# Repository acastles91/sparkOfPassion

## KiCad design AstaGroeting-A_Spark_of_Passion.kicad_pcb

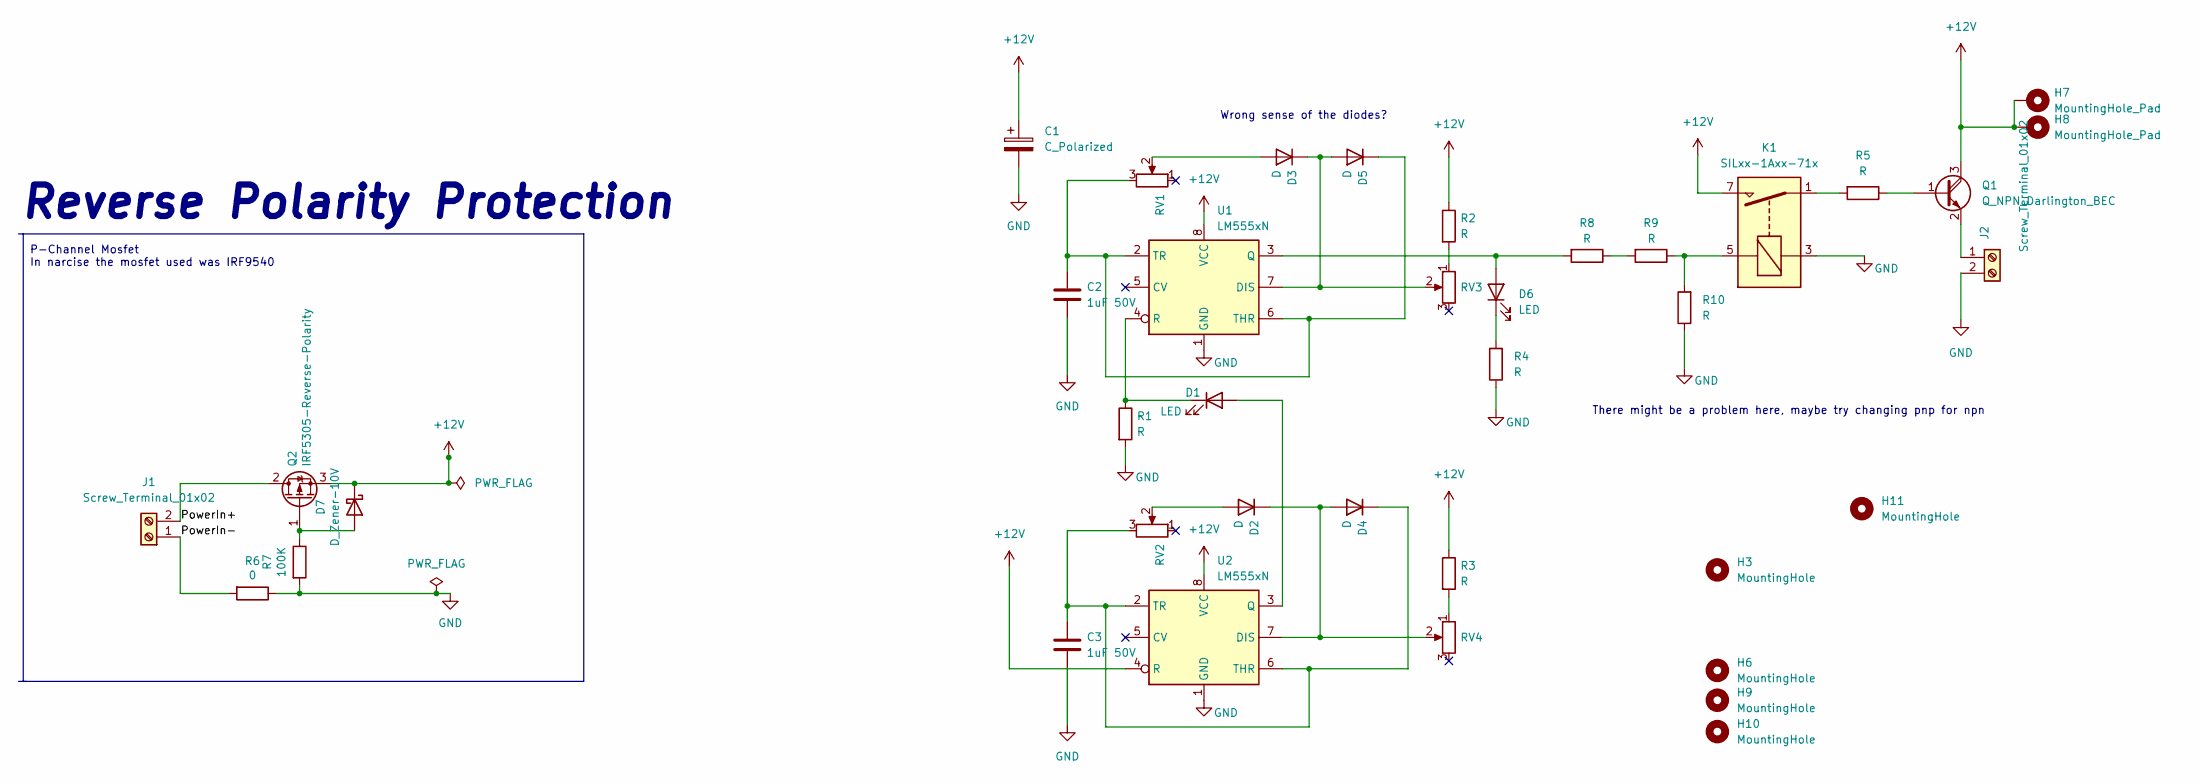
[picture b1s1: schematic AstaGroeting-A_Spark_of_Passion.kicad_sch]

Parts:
C1: C_Polarized; CP_Radial_D13.0mm_P5.00mm
C2, C3: 1uF 50V; CP_Radial_D4.0mm_P2.00mm
D1, D6: LED; LED_D3.0mm
D2, D3, D4, D5: D; D_A-405_P10.16mm_Horizontal
D7: D_Zener-10V; D_DO-35_SOD27_P7.62mm_Horizontal
H3, H6, H9, H10, H11: MountingHole; MountingHole_3.2mm_M3_Pad_Via
H7, H8: MountingHole_Pad; MountingHole_4.3mm_M4_Pad_Via
J1, J2: Screw_Terminal_01x02; TerminalBlock_Altech_AK300-2_P5.00mm
K1: SILxx-1Axx-71x; Relay_SPST_StandexMeder_SIL_Form1A
Q1: Q_NPN_Darlington_BEC; TO-3
Q2: IRF5305-Reverse-Polarity; TO-220-3_Horizontal_TabDown
R1, R2, R3, R4, R5, R8, R9, R10: R; R_Axial_DIN0207_L6.3mm_D2.5mm_P10.16mm_Horizontal
R6: 0; R_Axial_DIN0207_L6.3mm_D2.5mm_P10.16mm_Horizontal
R7: 100K; R_Axial_DIN0207_L6.3mm_D2.5mm_P10.16mm_Horizontal
RV1, RV2, RV3, RV4: R_Potentiometer; Potentiometer_Bourns_3296W_Vertical
U1, U2: LM555xN; DIP-8_W7.62mm

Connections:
+12V: C1.1, D7.1 (K), H7.1, H8.1, K1.7, Q1.3 (C), Q2.3 (S), R2.1, R3.1, U1.8 (VCC), U2.4 (R), U2.8 (VCC)
/PowerIn+: J1.2, Q2.2 (D)
/PowerIn-: J1.1, R6.2
GND: C1.2, C2.2, C3.2, J2.2, K1.3, R1.2, R4.1, R6.1, R7.2, R10.1, U1.1 (GND), U2.1 (GND)
unnamed: C2.1, D5.1 (K), RV1.3, U1.2 (TR), U1.6 (THR)
unnamed: C3.1, D4.1 (K), RV2.3, U2.2 (TR), U2.6 (THR)
unnamed: D1.1 (K), R1.1, U1.4 (R)
unnamed: D1.2 (A), U2.3 (Q)
unnamed: D2.1 (K), D4.2 (A), RV4.2, U2.7 (DIS)
unnamed: D2.2 (A), RV2.2
unnamed: D3.1 (K), D5.2 (A), RV3.2, U1.7 (DIS)
unnamed: D3.2 (A), RV1.2
unnamed: D6.1 (K), R4.2
unnamed: D6.2 (A), R8.2, U1.3 (Q)
unnamed: D7.2 (A), Q2.1 (G), R7.1
unnamed: K1.1, R5.2
unnamed: K1.5, R9.1, R10.2
unnamed: Q1.1 (B), R5.1
unnamed: J2.1, Q1.2 (E)
unnamed: R2.2, RV3.1
unnamed: R3.2, RV4.1
unnamed: R8.1, R9.2

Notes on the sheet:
Reverse Polarity Protection
Wrong sense of the diodes?
There might be a problem here, maybe try changing pnp for npn
P-Channel Mosfet In narcise the mosfet used was IRF9540

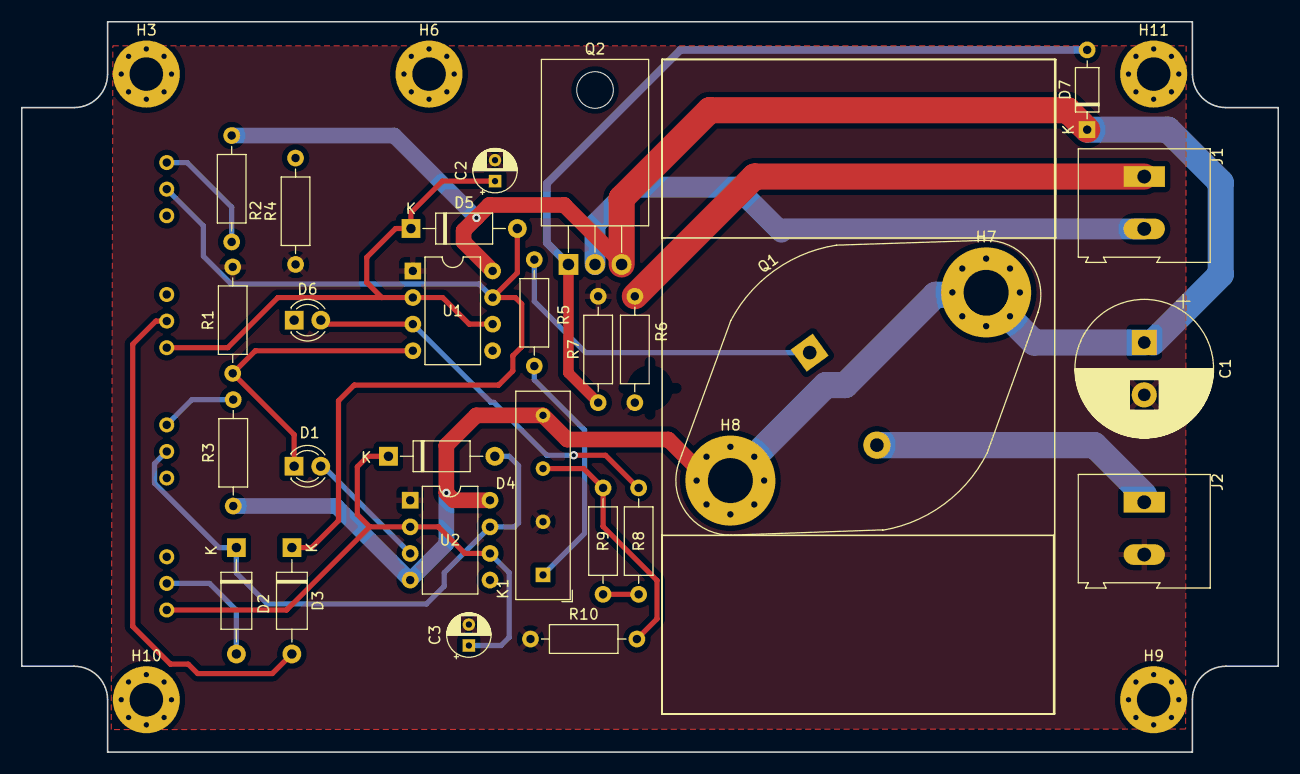
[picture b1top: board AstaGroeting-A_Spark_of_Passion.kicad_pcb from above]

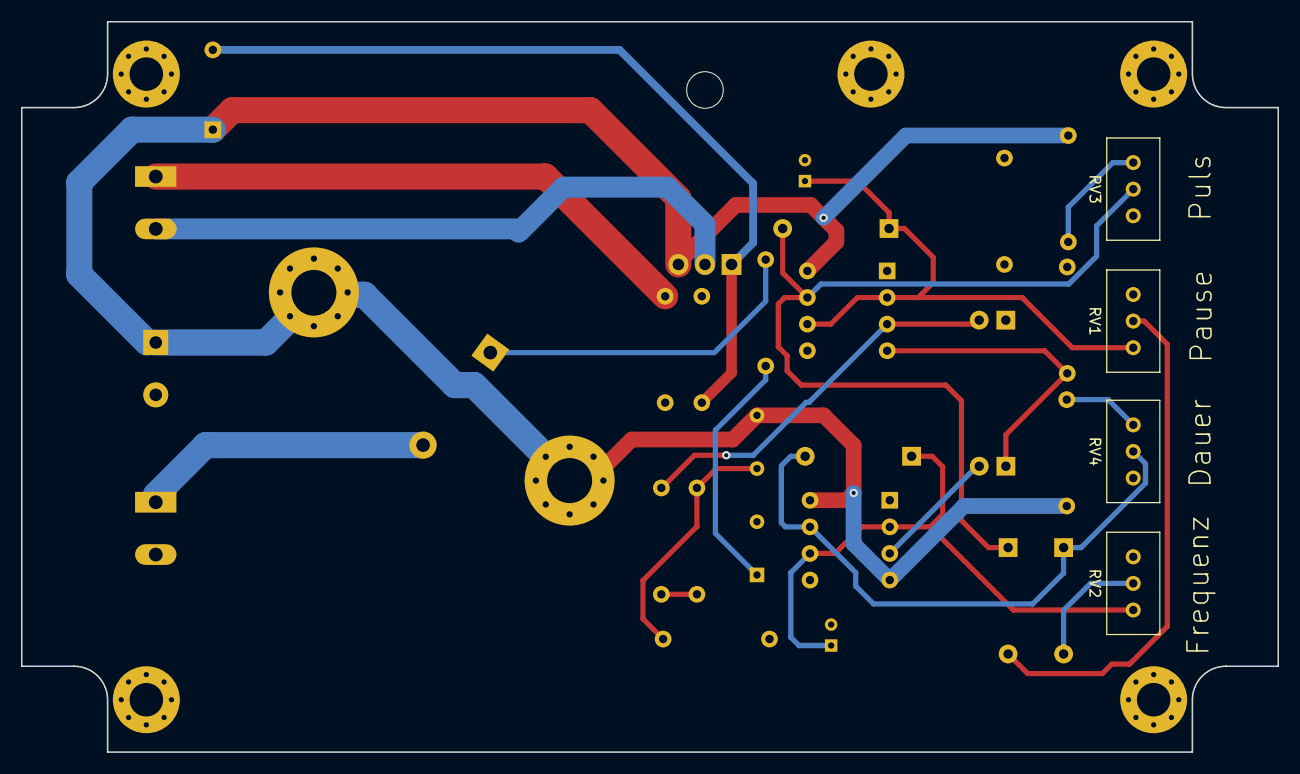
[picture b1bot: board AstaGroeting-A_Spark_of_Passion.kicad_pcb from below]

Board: 2 copper layers, 120.0 x 69.8 mm, 38 parts (4 on the bottom side), 22 nets.
